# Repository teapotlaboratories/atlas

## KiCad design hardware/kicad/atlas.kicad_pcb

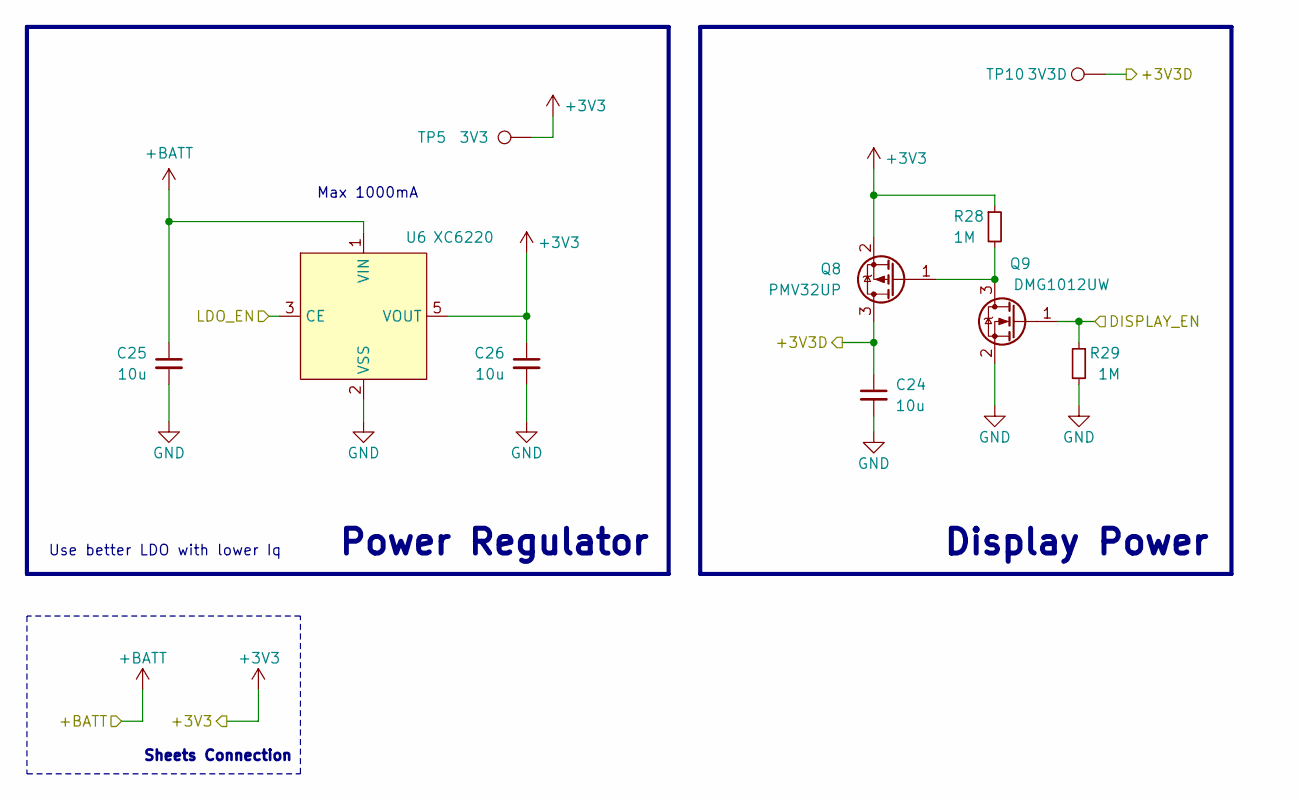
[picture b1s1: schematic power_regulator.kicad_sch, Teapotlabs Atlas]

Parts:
C24, C25, C26: 10u; C_0603_1608Metric; Part Description Ceramic Capacitor 10V 10uF X5R ±10% 0603
Q8: PMV32UP; SOT-23; Part Description MOSFET P Channel 20V 4A 52mΩ@4.5V
Q9: DMG1012UW; SOT-323_SC-70; Part Description MOSFET N Channel 20V 1A 450mΩ@4.5V 600m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
R28, R29: 1M; R_0402_1005Metric; Part Description Resistor 62.5mW ±1% 1MΩ
TP5: 3V3; TestPoint_Pad_D1.0mm
TP10: 3V3D; TestPoint_Pad_D1.0mm
U6: XC6220; SOT-23-5; Part Description LDO Voltage Regulators 1A

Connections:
/+3V3D: C24.1, Q8.3 (D), TP10.1; also elsewhere on the board
/Main Controller/DISPLAY_EN: Q9.1 (G), R29.1; also elsewhere on the board
/Power Regulator/LDO_EN: U6.3 (CE); also elsewhere on the board
unnamed: Q8.1 (G), Q9.3 (D), R28.2

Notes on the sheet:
Use better LDO with lower Iq
Max 1000mA
Display Power
Sheets Connection
Power Regulator

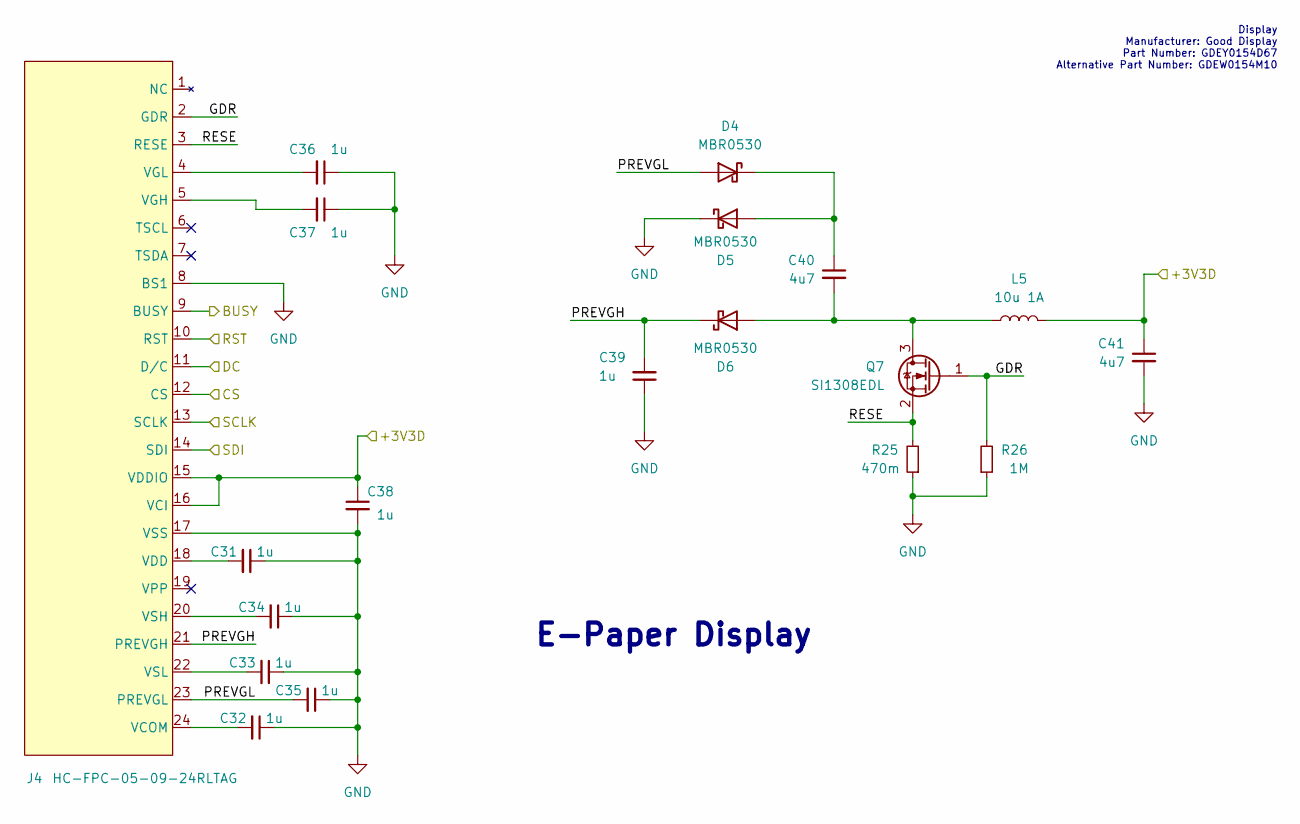
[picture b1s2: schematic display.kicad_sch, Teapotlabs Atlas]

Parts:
C31, C32, C33, C34, C35, C36, C37, C38, C39: 1u; C_0402_1005Metric; Part Description Ceramic Capacitors 50V 1uF X5R ±10%
C40, C41: 4u7; C_0603_1608Metric; Part Description Ceramic Capacitors 25V 4.7uF X5R ±10%
D4, D5, D6: MBR0530; D_SOD-123; Part Description Schottky Barrier Diodes 30V 430mV@500mA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
J4: HC-FPC-05-09-24RLTAG; FPC-SMD_24P-P0.50_HC-FPC-05-09-24RLTAG; Part Description FFC & FPC Connectors Clamshell 24P Bott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
L5: 10u 1A; L_Changjiang_FNR4012S; Part Description Power Inductors 1A 10uH ±20% 1.1A SMD,4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
Q7: SI1308EDL; SOT-323_SC-70; Part Description MOSFET N Channel 30V 1.4A 132mΩ@10V,1.4A
R25: 470m; R_0402_1005Metric; Part Description Resistor 125mW ±1% 470mΩ
R26: 1M; R_0402_1005Metric; Part Description Resistors 100mW ±1% 1MΩ

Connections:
/+3V3D: C38.1, C41.1, J4.15 (VDDIO), J4.16 (VCI), L5.1; also elsewhere on the board
/Display/BUSY: J4.9 (BUSY); also elsewhere on the board
/Display/CS: J4.12 (CS); also elsewhere on the board
/Display/DC: J4.11 (D/C); also elsewhere on the board
/Display/GDR: J4.2 (GDR), Q7.1 (G), R26.2
/Display/PREVGH: C39.2, D6.1 (K), J4.21 (PREVGH)
/Display/PREVGL: C35.2, D4.2 (A), J4.23 (PREVGL)
/Display/RESE: J4.3 (RESE), Q7.2 (S), R25.2
/Display/RST: J4.10 (RST); also elsewhere on the board
/Display/SCLK: J4.13 (SCLK); also elsewhere on the board
/Display/SDI: J4.14 (SDI); also elsewhere on the board
unnamed: C40.1, D4.1 (K), D5.2 (A)
unnamed: C40.2, D6.2 (A), L5.2, Q7.3 (D)
unnamed: C32.2, J4.24 (VCOM)
unnamed: C31.2, J4.18 (VDD)
unnamed: C37.2, J4.5 (VGH)
unnamed: C36.2, J4.4 (VGL)
unnamed: C34.2, J4.20 (VSH)
unnamed: C33.2, J4.22 (VSL)

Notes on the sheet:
Display Manufacturer: Good Display Part Number: GDEY0154D67 Alternative Part Number: GDEW0154M10
E-Paper Display

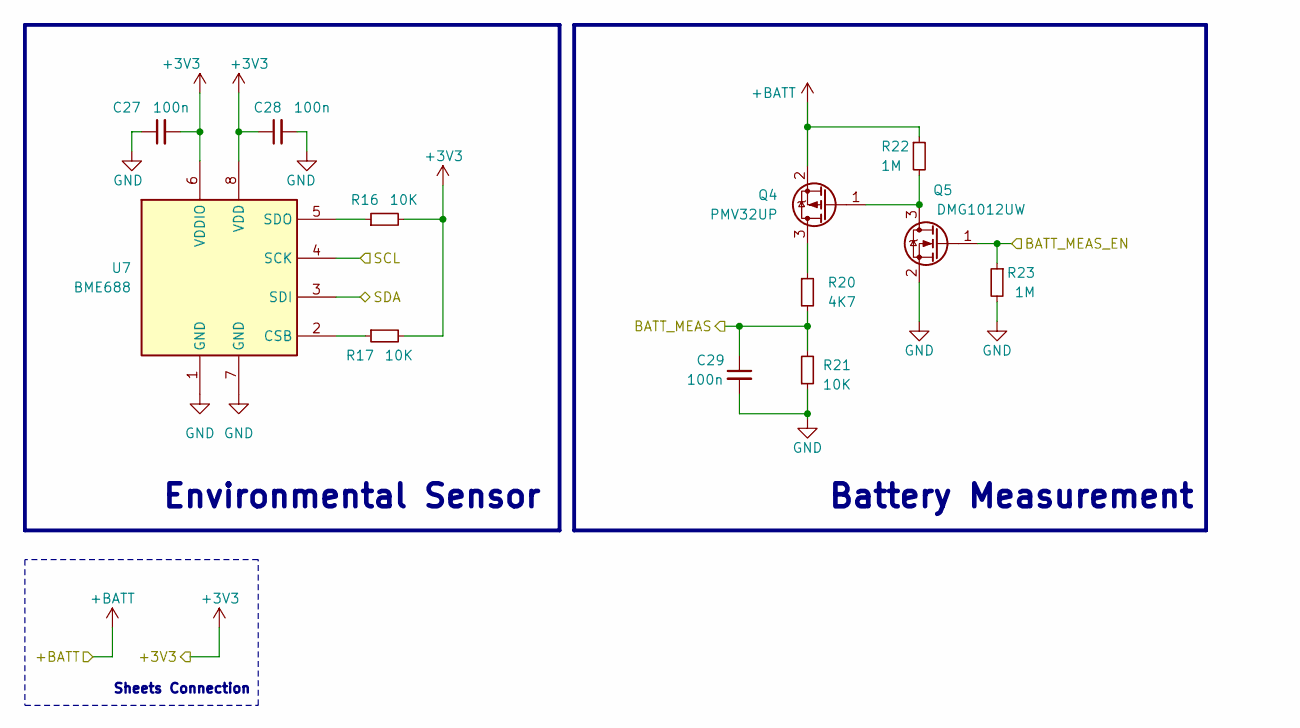
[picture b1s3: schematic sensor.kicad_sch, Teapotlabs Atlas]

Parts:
C27, C28, C29: 100n; C_0402_1005Metric; Part Description Ceramic Capacitor 16V 100nF X7R ±10%
Q4: PMV32UP; SOT-23; Part Description MOSFET P Channel 20V 4A 52mΩ@4.5V
Q5: DMG1012UW; SOT-323_SC-70; Part Description MOSFET N Channel 20V 1A 450mΩ@4.5V 600m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
R16, R17, R21: 10K; R_0402_1005Metric; Part Description Resistors 62.5mW ±1% 10kΩ
R20: 4K7; R_0402_1005Metric; Part Description Resistor 62.5mW ±1% 4.7kΩ
R22, R23: 1M; R_0402_1005Metric; Part Description Resistor 62.5mW ±1% 1MΩ
U7: BME688; BME680-PSON80P300X300X100-8N; Part Description Gas, Humidity, Pressure, Temperature Se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

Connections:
/Main Controller/BATT_MEAS: C29.1, R20.2, R21.2; also elsewhere on the board
/Main Controller/BATT_MEAS_EN: Q5.1 (G), R23.1; also elsewhere on the board
/SCL: U7.4 (SCK); also elsewhere on the board
/SDA: U7.3 (SDI); also elsewhere on the board
unnamed: Q4.3 (D), R20.1
unnamed: Q4.1 (G), Q5.3 (D), R22.2
unnamed: R17.1, U7.2 (CSB)
unnamed: R16.1, U7.5 (SDO)

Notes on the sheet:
Sheets Connection
Battery Measurement
Environmental Sensor

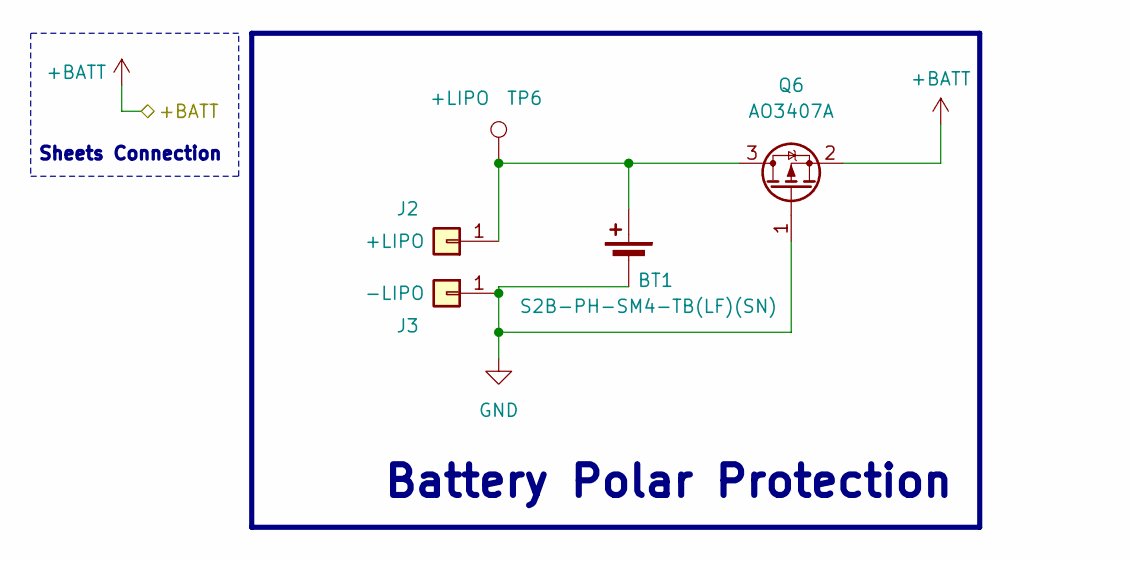
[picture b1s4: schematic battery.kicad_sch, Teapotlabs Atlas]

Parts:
BT1: S2B-PH-SM4-TB(LF)(SN); JST_PH_S2B-PH-SM4-TB_1x02-1MP_P2.00mm_Horizontal; Part Description Wire To Board Connector 1x2P PH 2mm Mal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
J2: +LIPO; TestPoint_THTPad_D1.0mm_Drill0.5mm; Part Description On-board Pad
J3: -LIPO; TestPoint_THTPad_D1.0mm_Drill0.5mm; Part Description On-board Pad
Q6: AO3407A; SOT-23; Part Description MOSFET P Channel 30V 4.3A 48mΩ@10V,4.3A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
TP6: +LIPO; TestPoint_Pad_D1.0mm

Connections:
unnamed: BT1.1 (+), J2.1, Q6.3 (D), TP6.1

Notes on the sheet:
Battery Polar Protection
Sheets Connection

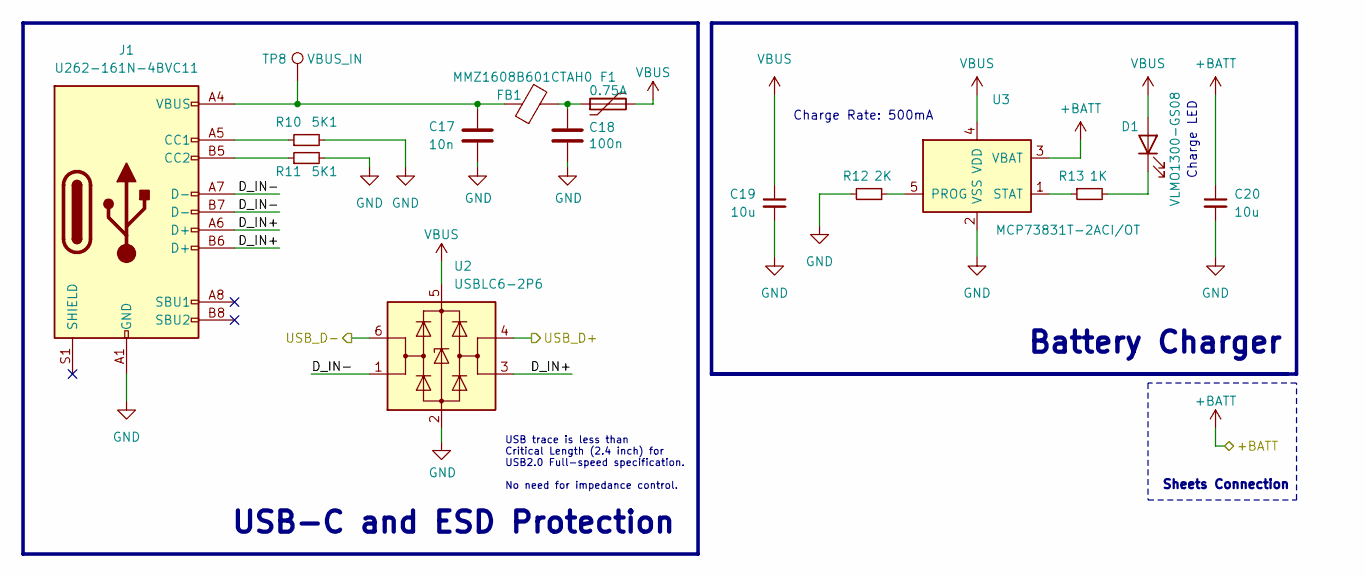
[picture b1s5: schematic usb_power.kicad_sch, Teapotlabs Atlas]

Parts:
C17: 10n; C_0402_1005Metric; Part Description Ceramic Capacitors 16V 10nF X7R ±10%
C18: 100n; C_0402_1005Metric; Part Description Ceramic Capacitor 16V 100nF X7R ±10%
C19, C20: 10u; C_0603_1608Metric; Part Description Ceramic Capacitor 10V 10uF X5R ±10% 0603
D1: VLMO1300-GS08; LED_0603_1608Metric; Part Description Orange 2V 20mA
F1: 0.75A; Fuse_0805_2012Metric; Part Description Resettable Fuses 6V 750mA 40A 1.5A
FB1: MMZ1608B601CTAH0; L_0603_1608Metric; Part Description Ferrite Beads 400mΩ ±25% 600Ω@100MHz
J1: U262-161N-4BVC11; USB_C_Receptacle_XKB_U262-16XN-4BVC11; Part Description USB Connectors Type-C 3A USB 3.1 16P
R10, R11: 5K1; R_0402_1005Metric; Part Description Resistor 62.5mW ±1% 5.1kΩ
R12: 2K; R_0402_1005Metric; Part Description Resistor 62.5mW ±1% 2kΩ
R13: 1K; R_0402_1005Metric; Part Description Resistor 62.5mW ±1% 1kΩ
TP8: VBUS_IN; TestPoint_Pad_D1.0mm
U2: USBLC6-2P6; SOT-666; Part Description ESD Protection 6V 17V 2 Unidirectional 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
U3: MCP73831T-2ACI/OT; SOT-23-5; Part Description Battery Management IC 6V LiPoly 1500mA

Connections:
/Main Controller/USB_D+: U2.4 (I/O2); also elsewhere on the board
/Main Controller/USB_D-: U2.6 (I/O1); also elsewhere on the board
/USB Power/D_IN+: J1.A6 (D+), J1.B6 (D+), U2.3 (I/O2)
/USB Power/D_IN-: J1.A7 (D-), J1.B7 (D-), U2.1 (I/O1)
unnamed: C17.1, FB1.1, J1.A4 (VBUS), J1.A9 (VBUS), J1.B4 (VBUS), J1.B9 (VBUS), TP8.1
unnamed: C18.1, F1.1, FB1.2
unnamed: D1.1 (K), R13.2
unnamed: J1.A5 (CC1), R10.1
unnamed: J1.B5 (CC2), R11.1
unnamed: R12.1, U3.5 (PROG)
unnamed: R13.1, U3.1 (STAT)
VBUS: C19.1, D1.2 (A), F1.2, U2.5 (VBUS), U3.4 (VDD)

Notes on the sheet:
Sheets Connection
Charge Rate: 500mA
Battery Charger
USB-C and ESD Protection
Charge LED
USB trace is less than Critical Length (2.4 inch) for USB2.0 Full-speed specification. No need for impedance control.

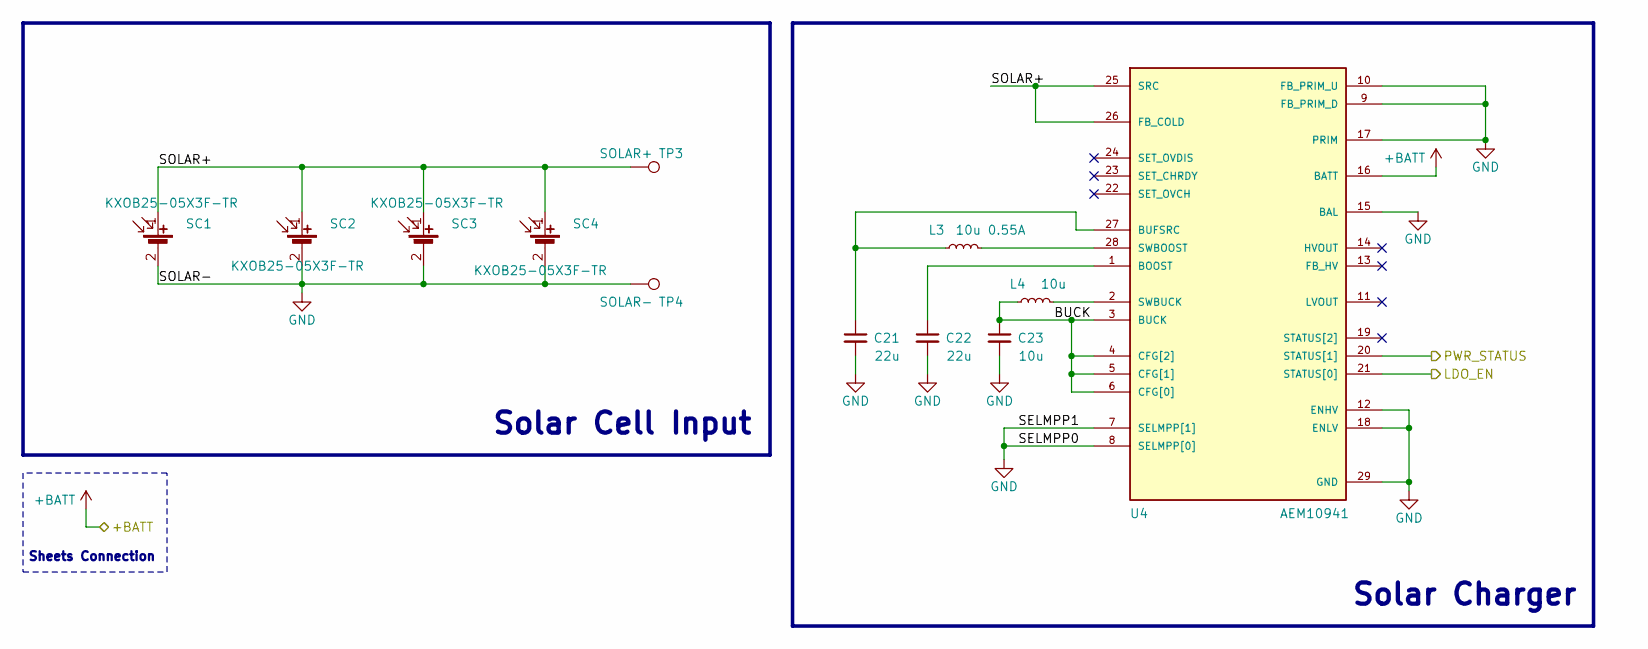
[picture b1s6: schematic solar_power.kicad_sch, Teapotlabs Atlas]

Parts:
C21, C22: 22u; C_0603_1608Metric; Part Description Ceramic Capacitors 10V 22uF X5R ±20%
C23: 10u; C_0603_1608Metric; Part Description Ceramic Capacitor 10V 10uF X5R ±10%
L3: 10u 0.55A; IND_LPS4012-103MRB; Part Description Power Inductors - SMD 10uH Shld 20% 1.1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
L4: 10u; L_0603_1608Metric; Part Description Power Inductors 10uH ±20% 90mA 1.05Ω
SC1, SC2, SC3, SC4: KXOB25-05X3F-TR; KXOB25-05X3F; Part Description Solar Cell G3 Thin 2.07V 30.7MW
TP3: SOLAR+; TestPoint_Pad_D1.0mm
TP4: SOLAR-; TestPoint_Pad_D1.0mm
U4: AEM10941; QFN-28-1EP_5x5mm_P0.5mm_EP3.35x3.35mm; Part Description PMIC IC - Photovoltaic Energy Harvestin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

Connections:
/Main Controller/PWR_STATUS: U4.20 (STATUS[1]); also elsewhere on the board
/Power Regulator/LDO_EN: U4.21 (STATUS[0]); also elsewhere on the board
/Solar Power/BUCK: C23.1, L4.1, U4.3 (BUCK), U4.4 (CFG[2]), U4.5 (CFG[1]), U4.6 (CFG[0])
/Solar Power/SOLAR+: SC1.1 (+), SC2.1 (+), SC3.1 (+), SC4.1 (+), TP3.1, U4.25 (SRC), U4.26 (FB_COLD)
unnamed: C22.1, U4.1 (BOOST)
unnamed: C21.1, L3.1, U4.27 (BUFSRC)
unnamed: L3.2, U4.28 (SWBOOST)
unnamed: L4.2, U4.2 (SWBUCK)

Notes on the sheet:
Solar Cell Input
Sheets Connection
Solar Charger

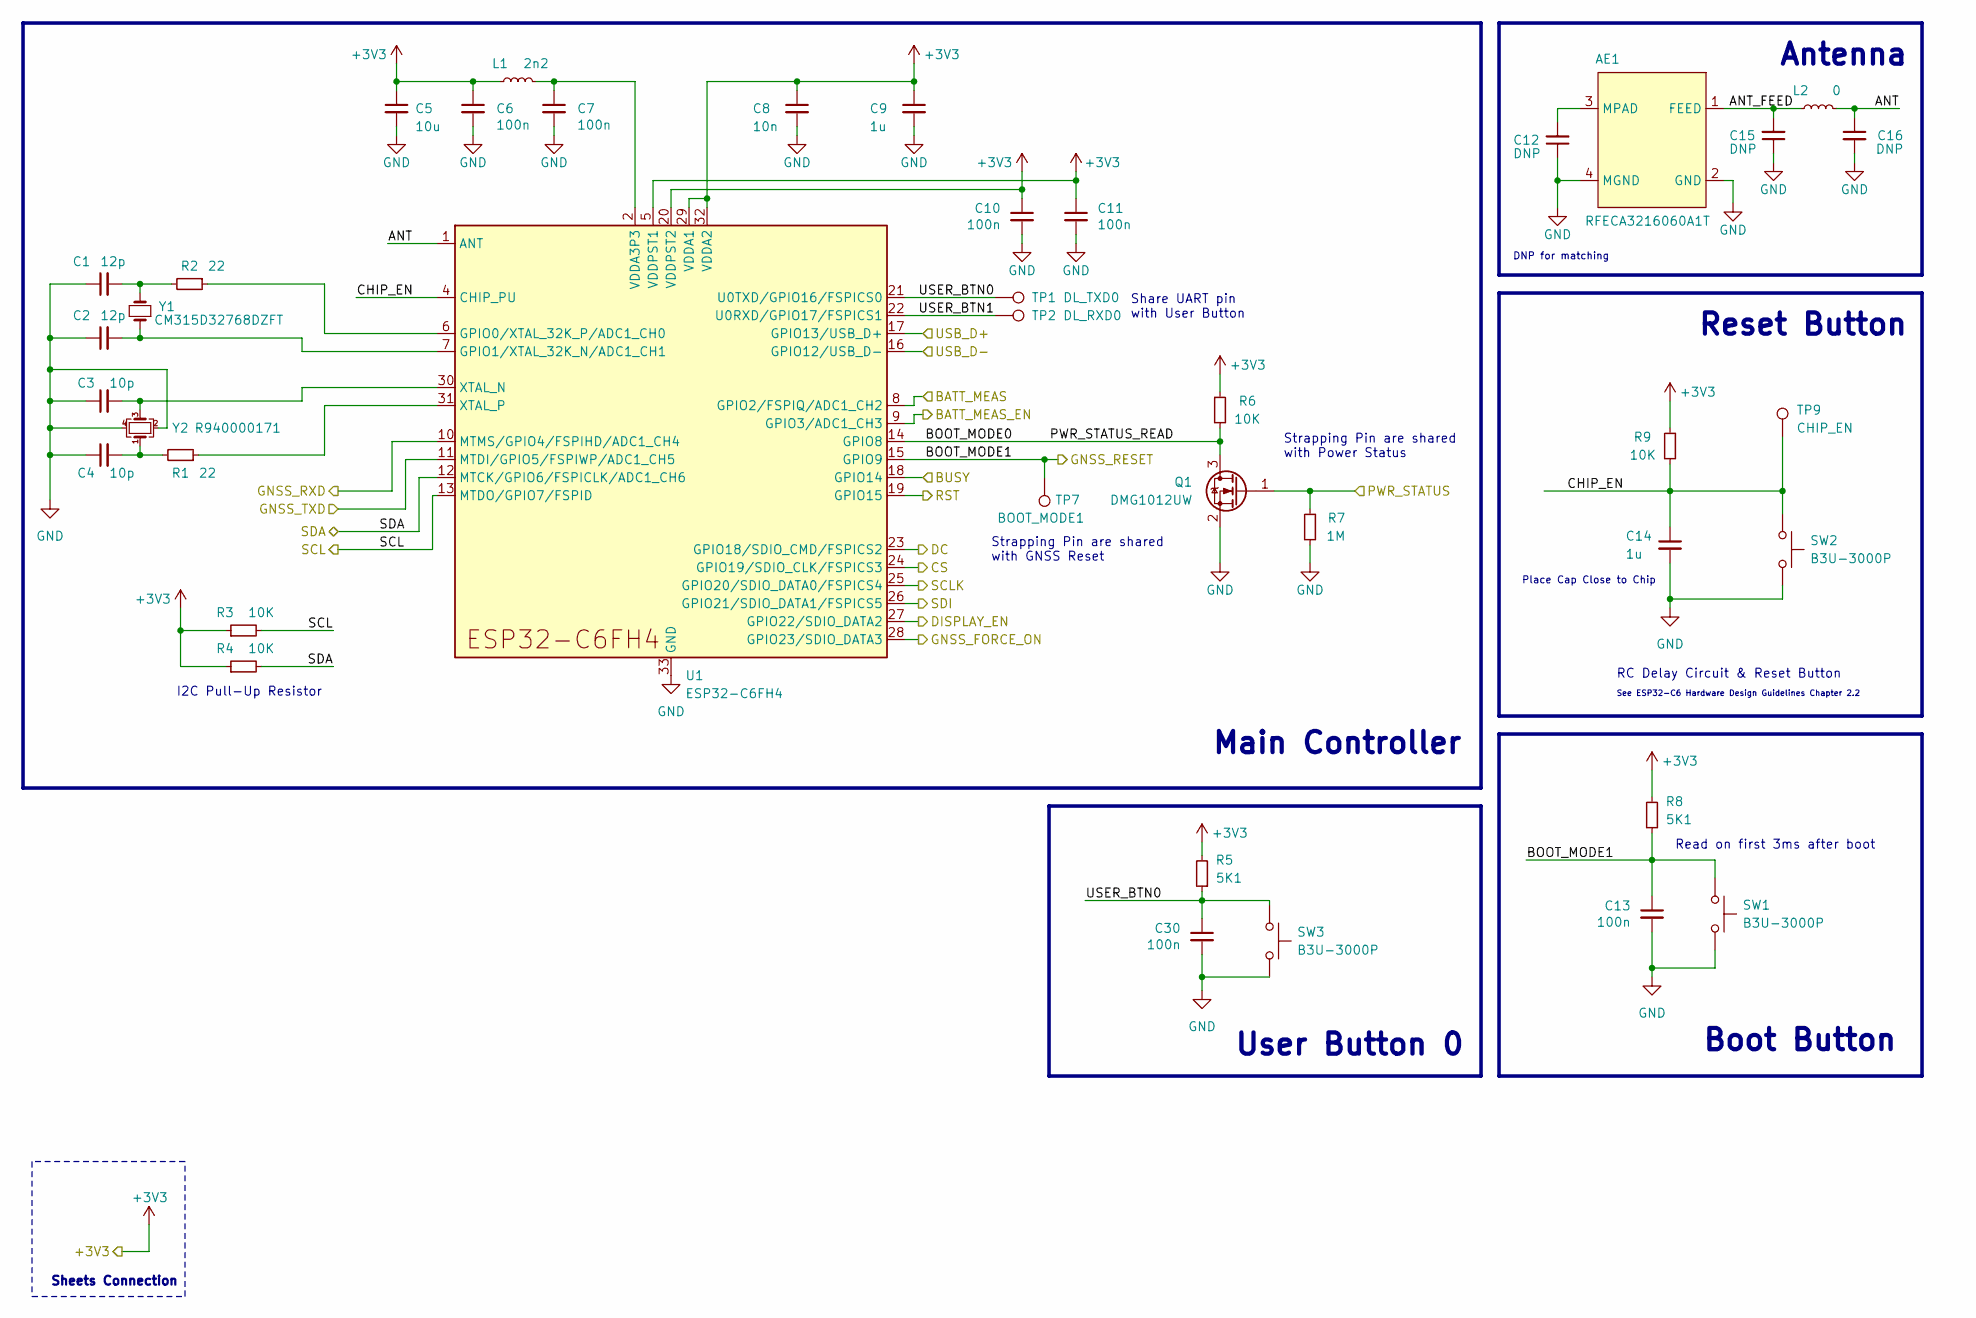
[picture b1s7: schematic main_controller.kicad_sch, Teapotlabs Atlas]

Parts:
AE1: RFECA3216060A1T; Part Description Chip RF Antenna 2.4GHz 2dBi
C1, C2: 12p; C_0402_1005Metric; Part Description Ceramic Capacitors 50V 12pF C0G ±1%
C3, C4: 10p; C_0402_1005Metric; Part Description Ceramic Capacitors 50V 10pF C0G ±1%
C5: 10u; C_0603_1608Metric; Part Description Ceramic Capacitor 10V 10uF X5R ±10% 0603
C6, C7, C10, C11, C13, C30: 100n; C_0402_1005Metric; Part Description Ceramic Capacitor 16V 100nF X7R ±10%
C8: 10n; C_0402_1005Metric; Part Description Ceramic Capacitors 16V 10nF X7R ±10%
C9, C14: 1u; C_0402_1005Metric; Part Description Ceramic Capacitors 10V 1uF X7R ±10%
C12, C15, C16: DNP; C_0402_1005Metric
L1: 2n2; L_0402_1005Metric; Part Description Power Inductors 2.53A 2.2nH ±2%
L2: 0; L_0402_1005Metric; Part Description Resistor 62.5mW ±1% 0Ω
Q1: DMG1012UW; SOT-323_SC-70; Part Description MOSFET N Channel 20V 1A 450mΩ@4.5V,600m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
R1, R2: 22; R_0402_1005Metric; Part Description Resistor 62.5mW ±1% 22Ω
R3, R4, R6, R9: 10K; R_0402_1005Metric; Part Description Resistors 62.5mW ±1% 10kΩ
R5, R8: 5K1; R_0402_1005Metric; Part Description Resistor 62.5mW ±1% 5.1kΩ
R7: 1M; R_0402_1005Metric; Part Description Resistor 62.5mW ±1% 1MΩ
SW1, SW2, SW3: B3U-3000P; SW_SPST_B3U-3000P; Part Description Tactile Switches NO 50mA 100MΩ 12V 1.59N
TP1: DL_TXD0; TestPoint_Pad_D1.0mm
TP2: DL_RXD0; TestPoint_Pad_D1.0mm
TP7: BOOT_MODE1; TestPoint_Pad_D1.0mm
TP9: CHIP_EN; TestPoint_Pad_D1.0mm
U1: ESP32-C6FH4; QFN-32-1EP_5x5mm_P0.5mm_EP3.6x3.6mm; Part Description Wireless SOC Bluetooth, WiFi Bluetooth 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
Y1: CM315D32768DZFT; Crystal_SMD_3215-2Pin_3.2x1.5mm; Part Description Crystals 32.768kHz 12.5pF ±20ppm
Y2: R940000171; Crystal_SMD_2016-4Pin_2.0x1.6mm; Part Description Crystals 40MHz 9pF ±10ppm

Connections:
/Display/BUSY: U1.18 (GPIO14); also elsewhere on the board
/Display/CS: U1.24 (GPIO19/SDIO_CLK/FSPICS3); also elsewhere on the board
/Display/DC: U1.23 (GPIO18/SDIO_CMD/FSPICS2); also elsewhere on the board
/Display/RST: U1.19 (GPIO15); also elsewhere on the board
/Display/SCLK: U1.25 (GPIO20/SDIO_DATA0/FSPICS4); also elsewhere on the board
/Display/SDI: U1.26 (GPIO21/SDIO_DATA1/FSPICS5); also elsewhere on the board
/GNSS/GNSS_RXD: U1.10 (MTMS/GPIO4/FSPIHD/ADC1_CH4); also elsewhere on the board
/GNSS/GNSS_TXD: U1.11 (MTDI/GPIO5/FSPIWP/ADC1_CH5); also elsewhere on the board
/Main Controller/ANT: C16.1, L2.2, U1.1 (ANT)
/Main Controller/ANT_FEED: AE1.1 (FEED), C15.2, L2.1
/Main Controller/BATT_MEAS: U1.8 (GPIO2/FSPIQ/ADC1_CH2); also elsewhere on the board
/Main Controller/BATT_MEAS_EN: U1.9 (GPIO3/ADC1_CH3); also elsewhere on the board
/Main Controller/BOOT_MODE0: Q1.3 (D), R6.2, U1.14 (GPIO8)
/Main Controller/BOOT_MODE1: C13.1, R8.1, SW1.1, TP7.1, U1.15 (GPIO9); also elsewhere on the board
/Main Controller/CHIP_EN: C14.1, R9.2, SW2.1, TP9.1, U1.4 (CHIP_PU)
/Main Controller/DISPLAY_EN: U1.27 (GPIO22/SDIO_DATA2); also elsewhere on the board
/Main Controller/PWR_STATUS: Q1.1 (G), R7.1; also elsewhere on the board
/Main Controller/USB_D+: U1.17 (GPIO13/USB_D+); also elsewhere on the board
/Main Controller/USB_D-: U1.16 (GPIO12/USB_D-); also elsewhere on the board
/Main Controller/USER_BTN0: C30.1, R5.1, SW3.1, TP1.1, U1.21 (U0TXD/GPIO16/FSPICS0)
/Main Controller/USER_BTN1: TP2.1, U1.22 (U0RXD/GPIO17/FSPICS1)
/SCL: R3.2, U1.13 (MTDO/GPIO7/FSPID); also elsewhere on the board
/SDA: R4.2, U1.12 (MTCK/GPIO6/FSPICLK/ADC1_CH6); also elsewhere on the board
unnamed: AE1.3 (MPAD), C12.2
unnamed: C7.1, L1.2, U1.2 (VDDA3P3), U1.3 (VDDA3P3)
unnamed: R2.1, U1.6 (GPIO0/XTAL_32K_P/ADC1_CH0)

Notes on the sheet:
Place Cap Close to Chip
Reset Button
Antenna
DNP for matching
Main Controller
Sheets Connection
User Button 0
Share UART pin with User Button
Boot Button
See ESP32-C6 Hardware Design Guidelines Chapter 2.2
RC Delay Circuit & Reset Button
Read on first 3ms after boot
I2C Pull-Up Resistor
Strapping Pin are shared with Power Status
Strapping Pin are shared with GNSS Reset

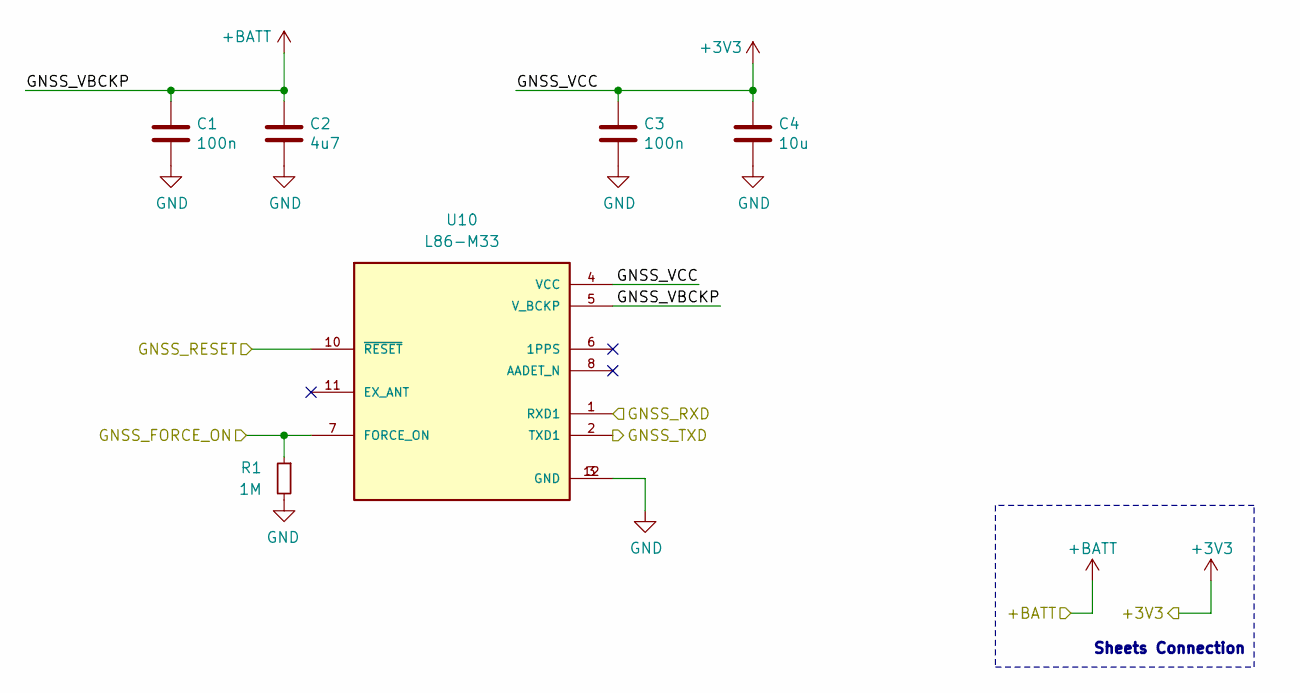
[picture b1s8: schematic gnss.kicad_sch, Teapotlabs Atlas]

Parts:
C1, C3: 100n; C_0603_1608Metric
C2: 4u7; C_0603_1608Metric
C4: 10u; C_0603_1608Metric
R1: 1M; R_0402_1005Metric
U10: L86-M33

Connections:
/GNSS/GNSS_RXD: U10.1 (RXD1); also elsewhere on the board
/GNSS/GNSS_TXD: U10.2 (TXD1); also elsewhere on the board
/Main Controller/BOOT_MODE1: U10.10 (~RESET); also elsewhere on the board

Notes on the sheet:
Sheets Connection

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
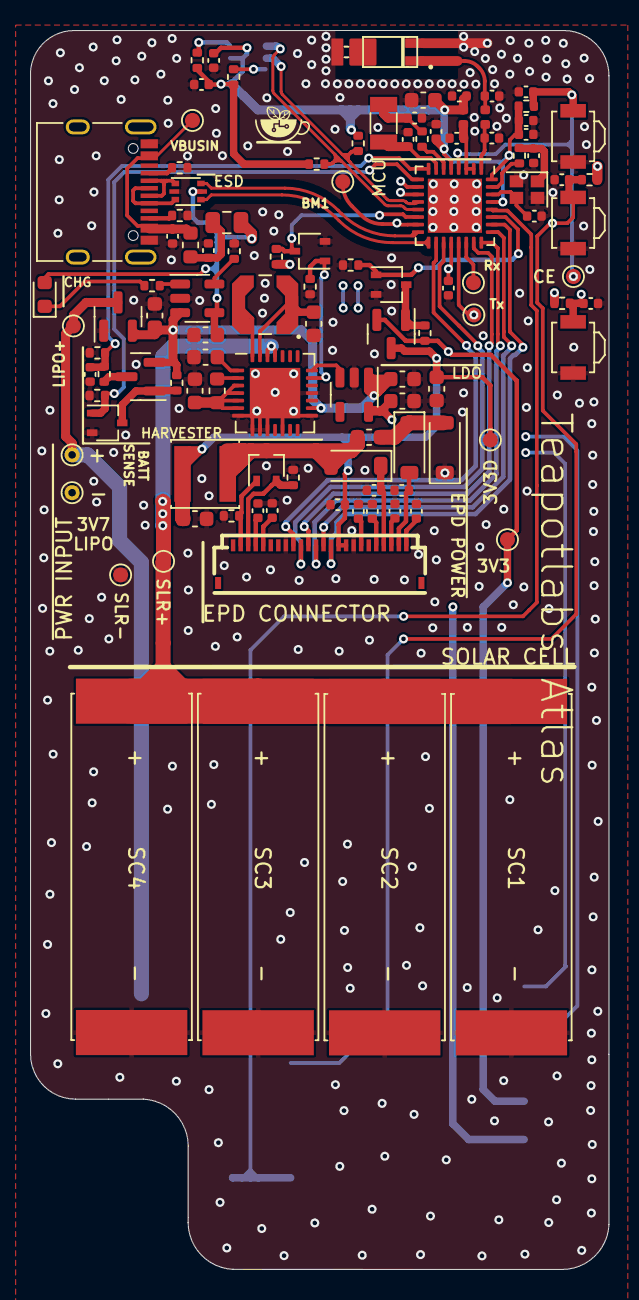
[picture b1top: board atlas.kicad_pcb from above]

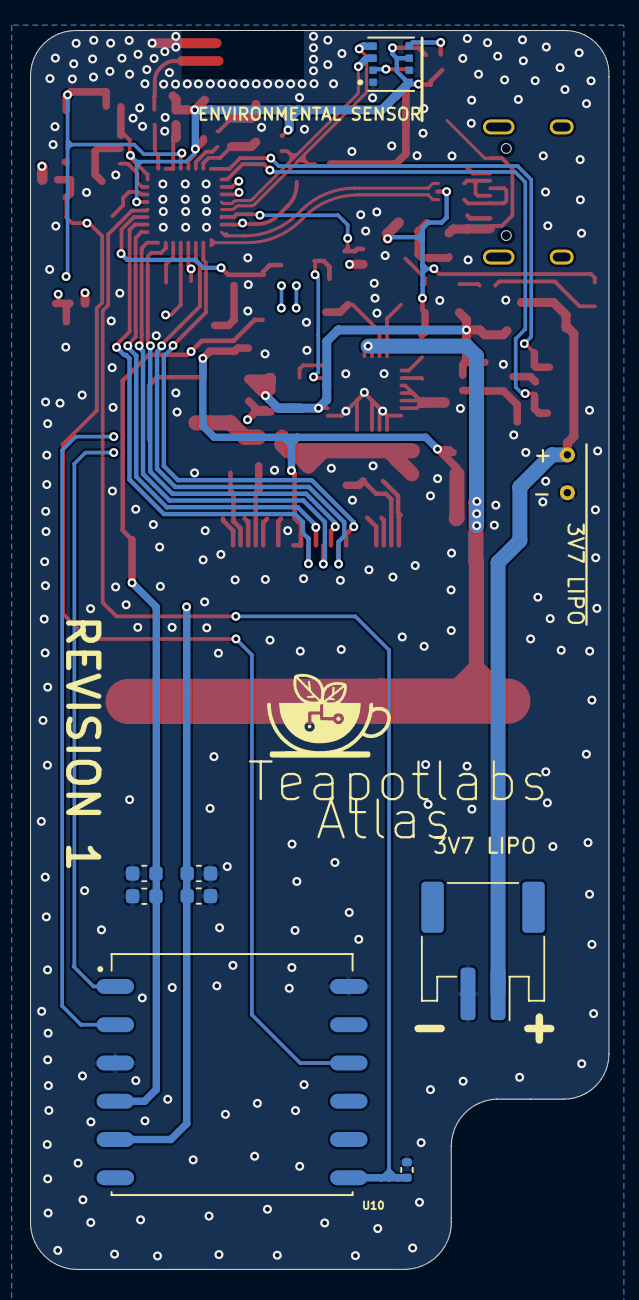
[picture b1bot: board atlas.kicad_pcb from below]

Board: 4 copper layers, 38.4 x 82.2 mm, 119 parts (8 on the bottom side), 71 nets.

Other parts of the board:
C42, C44: 100n; C_0603_1608Metric
C43: 4u7; C_0603_1608Metric
C45: 10u; C_0603_1608Metric
R15: 1M; R_0402_1005Metric

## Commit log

2024-10-19 initial upload
2024-10-20 update schematics with gnss
2024-10-20 update pcb
2024-10-20 update design
2024-10-20 update desgin
2024-10-20 clean-up
2024-10-21 Added a button for menu control (only pcb and no routing)
2024-10-22 add second user button
2024-10-22 added led symbols and placements on pcb.
2024-10-25 Revert "added led symbols and placements on pcb."
    This reverts commit 775bc6ae91366f689438663b29cde4e2220ca0a7.
2024-10-26 add gerber
2024-10-26 update schematics info
